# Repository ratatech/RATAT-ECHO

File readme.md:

# RATAT-ECHO

This repository contains mainly the PCB design files for a small echo effect unit. The circuit it's mainly composed by two major blocks, the echo and the spring reverb drive/recovery circuits. 

The echo module is basically an adaptation of the echo circuit included in PT2399 echo processor [datasheet](./datasheets/PT2399_1.pdf). The changes were mostly a few components values to a more standarized ones and the resistor/potentiometer to reduce a bit the minimum delay time. A great analysis of this circuit is done by [Electrosmash](https://www.electrosmash.com/pt2399-analysis). 

The core of the reverb unit is the [ Accutronics, AMC2BF, 2-Spring reverb tank](https://www.amplifiedparts.com/products/reverb-tank-accutronics-amc2bf-2-spring). This is a small and very affordable($9) spring reverb tank. I liked, not only for the budget but also because of the size and the ability to fit the whole tank within the unit box. The drive and recovery circuit was taken from Rod Eliott's design ["Spring Reverb Unit for Guitar"](https://sound-au.com/project34.htm). I added an additional potentiometer a the drive input in order to have some extra input gain. Also a clipping detector was included to have some feedback when pushing too much the input gain. 

## Files

* [datasheets](./datasheets) 	Datasheets of some of the components and schematics used in this project.
* [freecad](./freecad) 			Front panel 3d model design.
* [imgs](./imgs) 				Images used in the design and captures or the 3d models/final pcb.
* [kicad](./kicad) 				Main Kicad project directory. Including schematics and pcb.
* [others](./others) 			Random stuff.

---

## License

- **[MIT license](http://opensource.org/licenses/mit-license.php)**

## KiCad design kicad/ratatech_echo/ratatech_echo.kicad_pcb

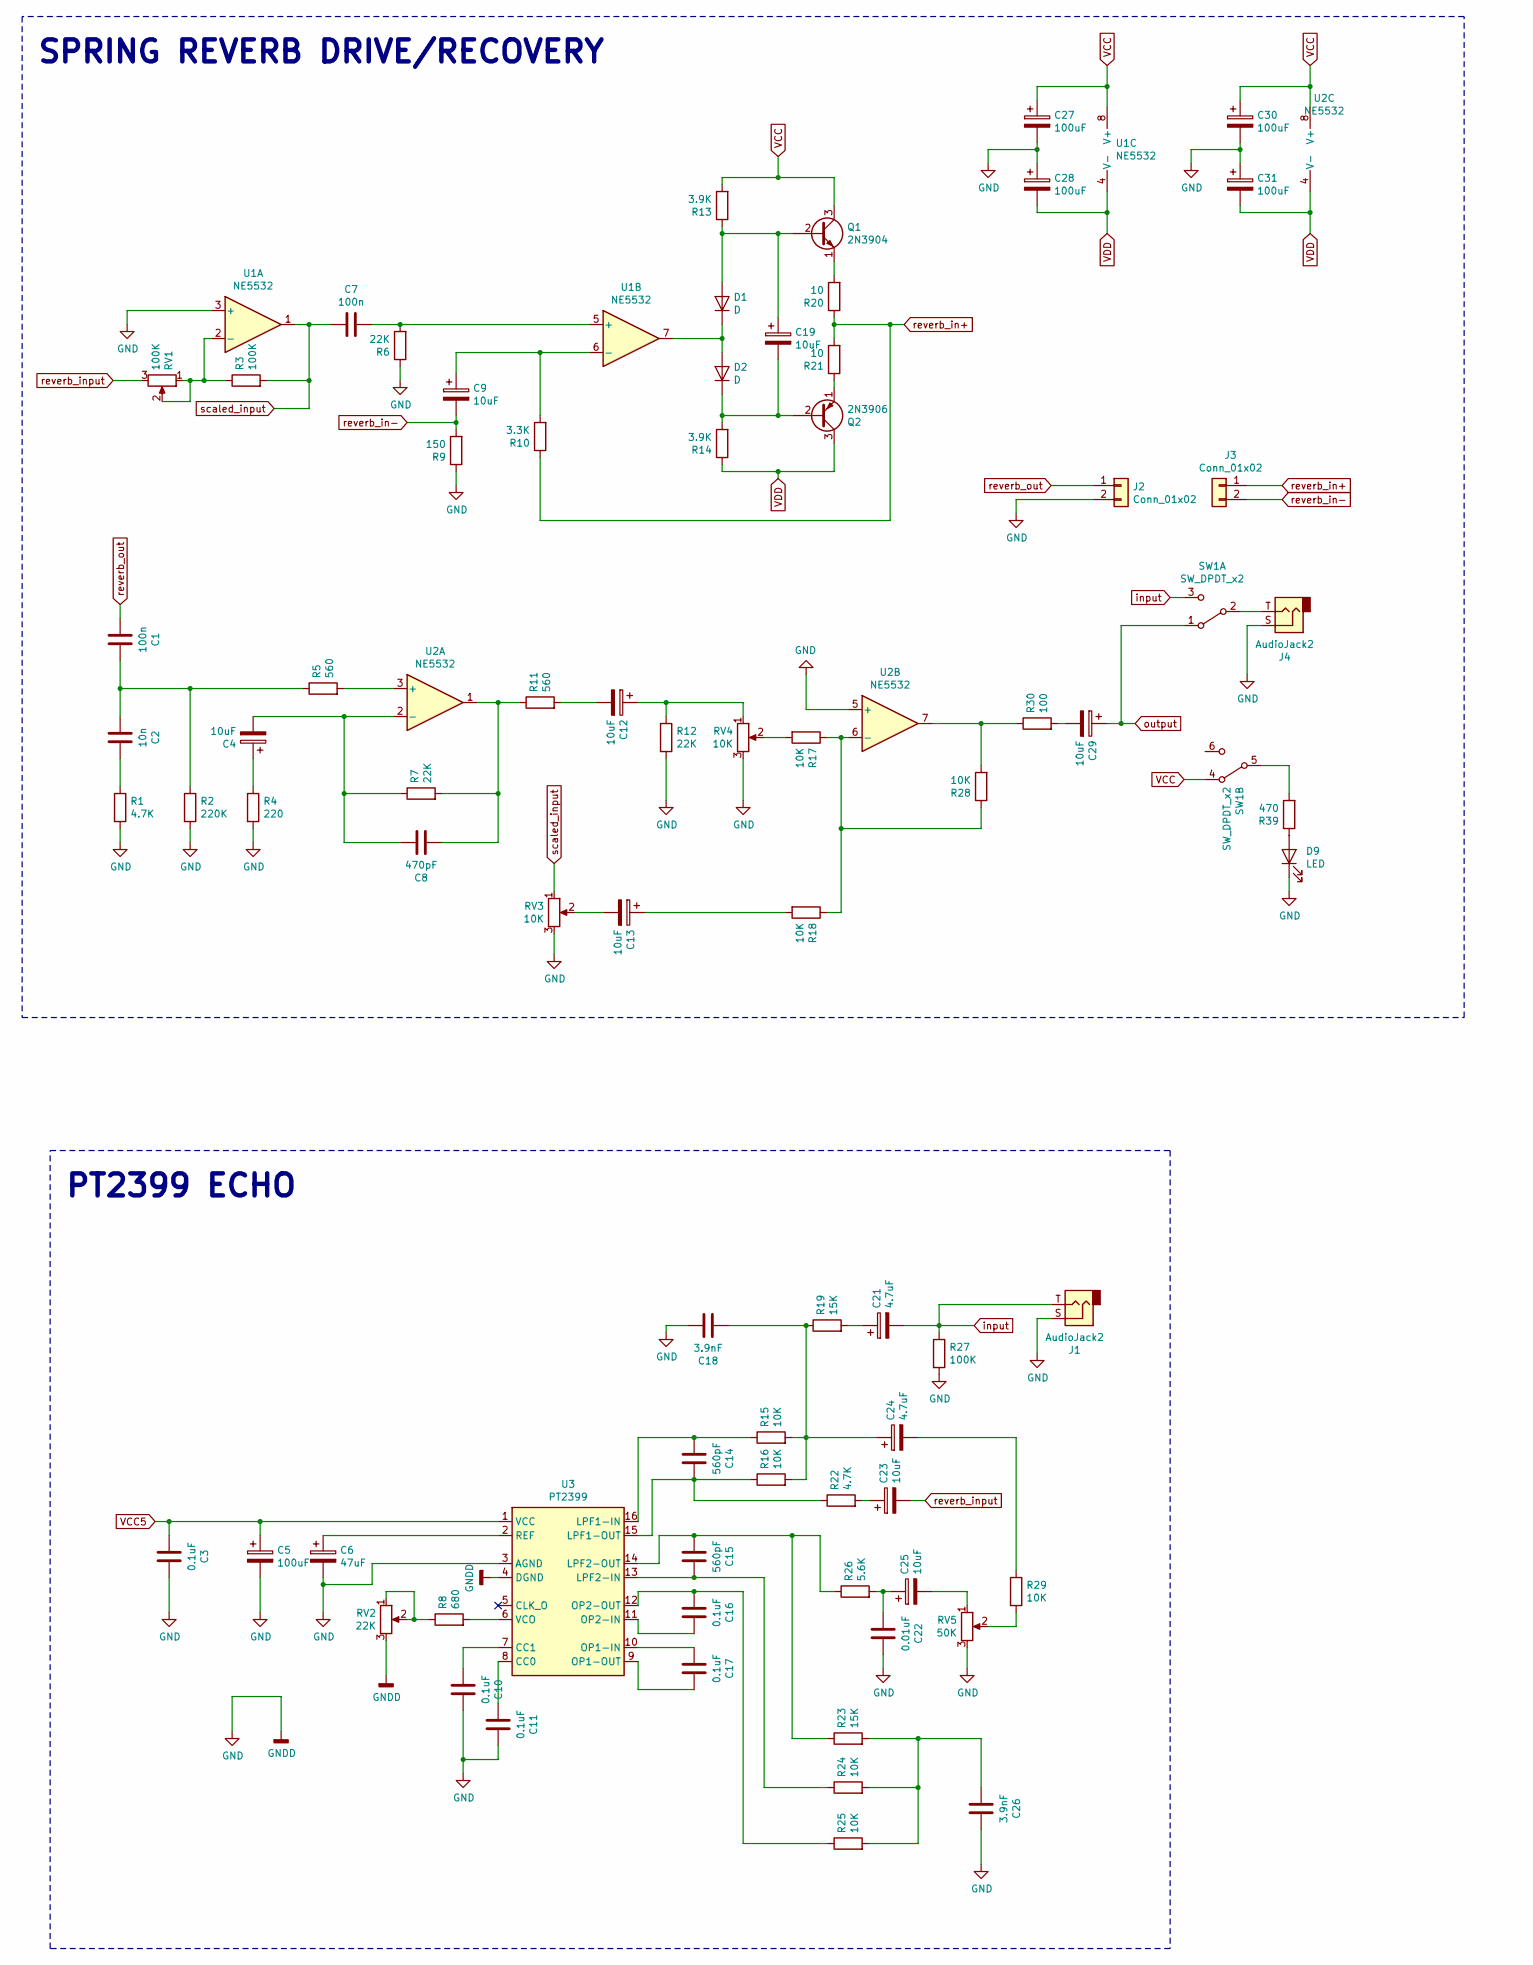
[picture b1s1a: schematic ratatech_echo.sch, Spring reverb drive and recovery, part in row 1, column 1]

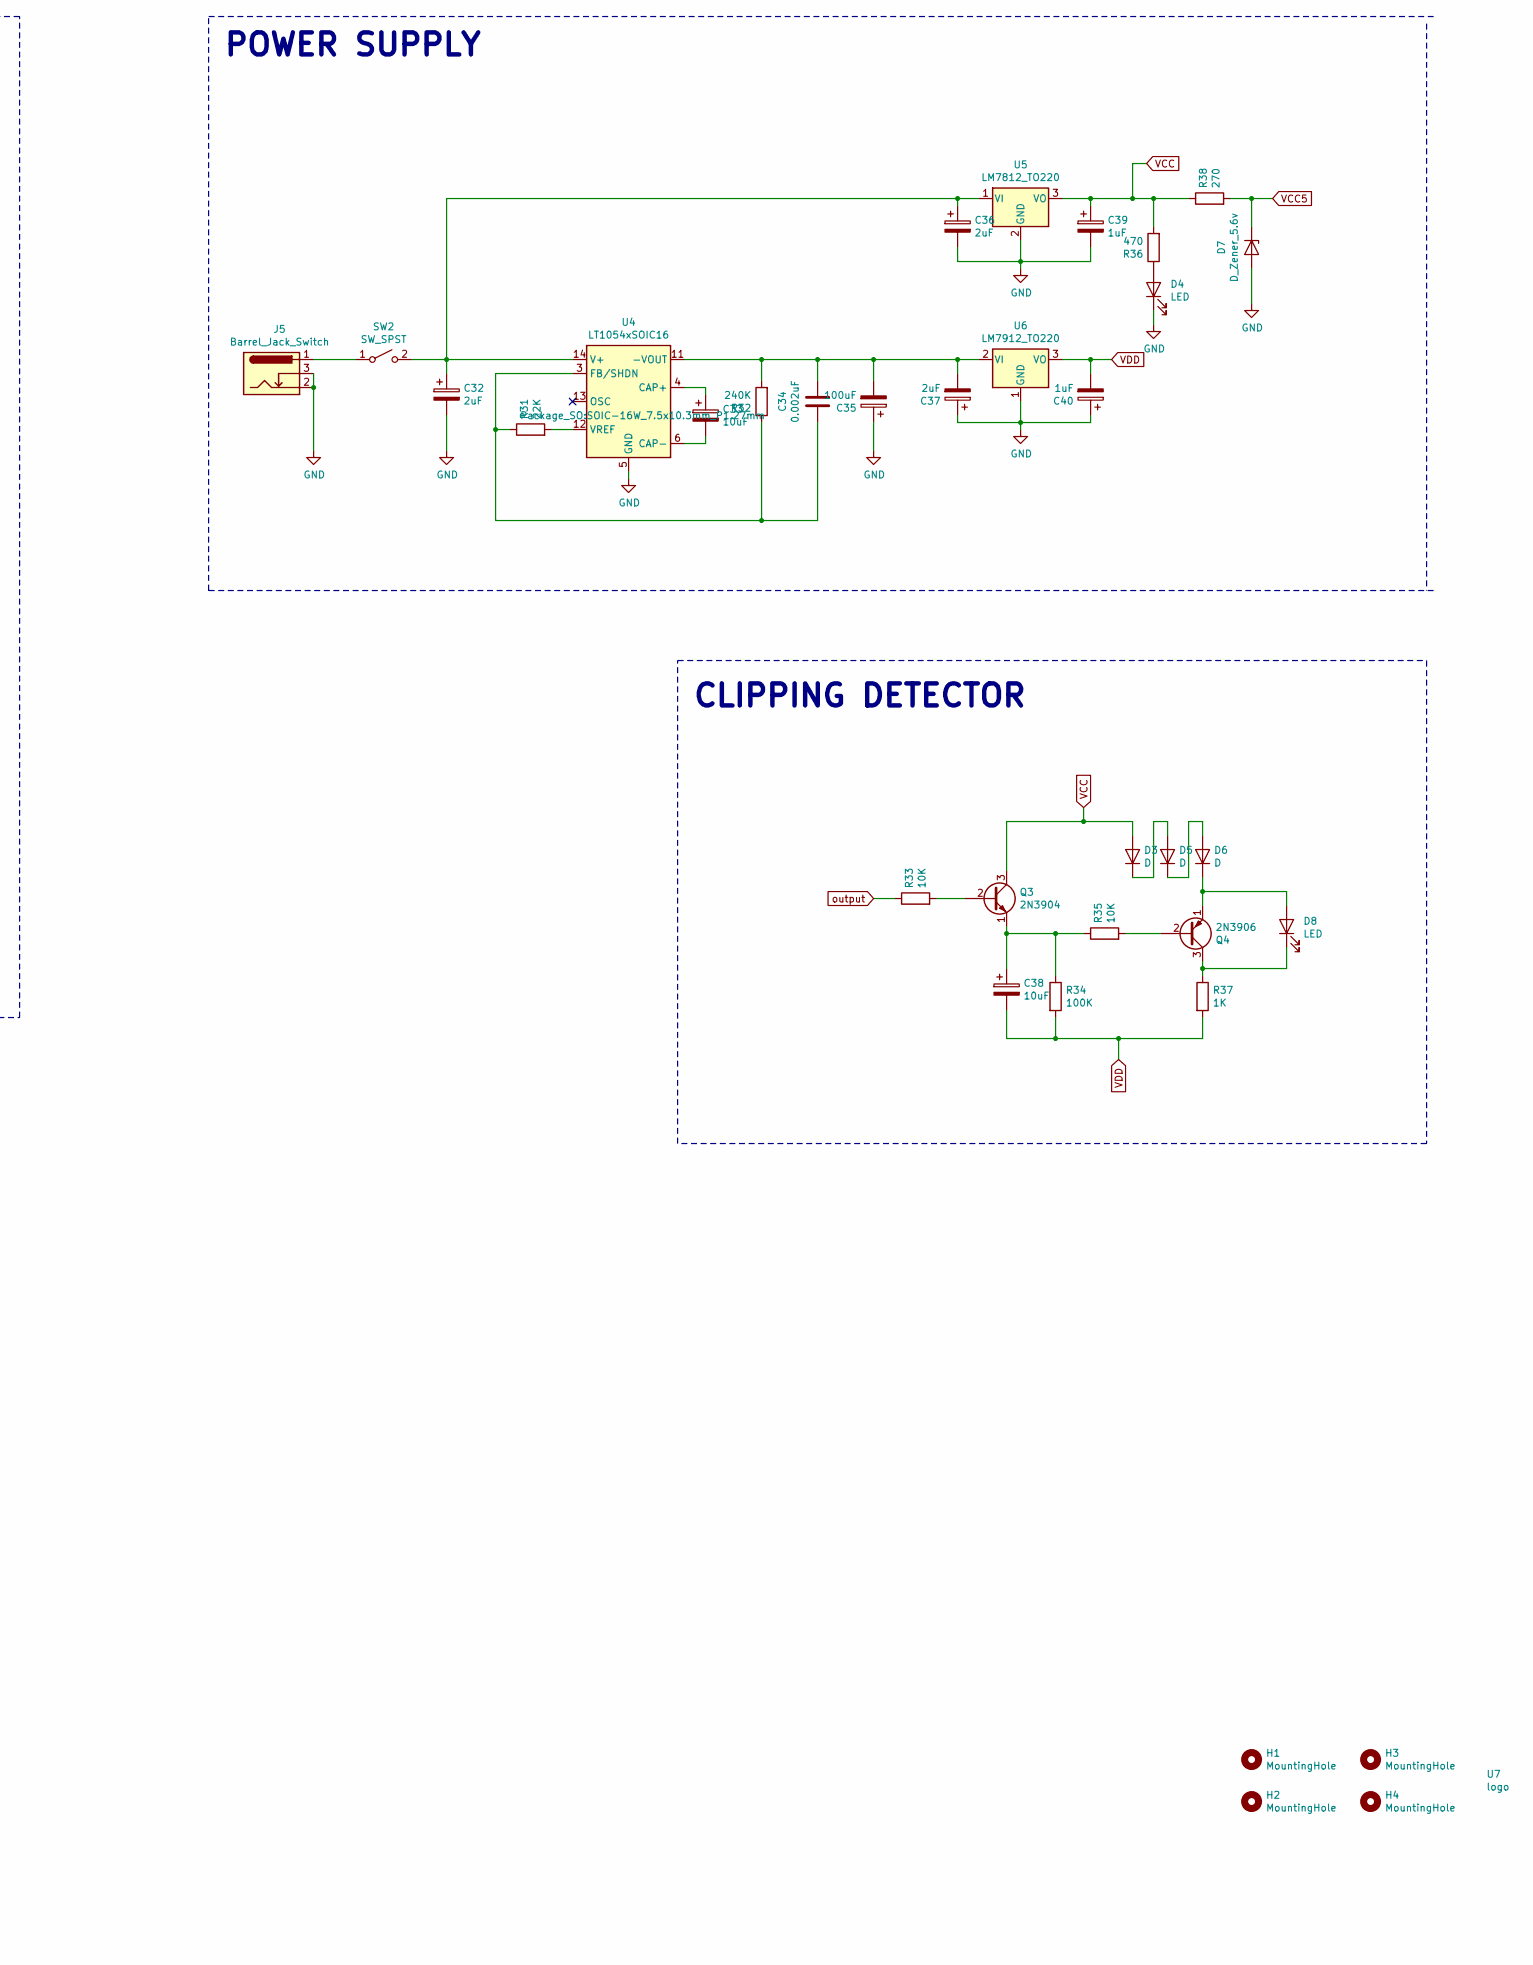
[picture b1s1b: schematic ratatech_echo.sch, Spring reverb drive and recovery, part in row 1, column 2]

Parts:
C1, C7: 100n; C_0603_1608Metric
C2: 10n; C_0603_1608Metric
C3, C10, C11, C16, C17: 0.1uF; C_0603_1608Metric
C4, C9, C12, C13, C19, C23, C25, C29, C33, C38: 10uF; CP_Elec_5x5.3
C5, C27, C28, C30, C31, C35: 100uF; CP_Elec_5x5.3
C6: 47uF; CP_Elec_5x5.3
C8: 470pF; C_0603_1608Metric
C14, C15: 560pF; C_0603_1608Metric
C18, C26: 3.9nF; C_0603_1608Metric
C21, C24: 4.7uF; CP_Elec_5x5.3
C22: 0.01uF; C_0603_1608Metric
C32, C36, C37: 2uF; CP_Elec_5x5.3
C34: 0.002uF; C_0603_1608Metric
C39, C40: 1uF; CP_Elec_5x5.3
D1, D2, D3, D5, D6: D; D_SOT-23_ANK
D4, D8, D9: LED; LED_1206_3216Metric
D7: D_Zener_5.6v; D_SOD-323
H1, H2, H3, H4: MountingHole; MountingHole_3mm
J1, J4: AudioJack2; Jack_6.35mm_Neutrik_NRJ4HF-1_Horizontal
J2, J3: Conn_01x02; JST_EH_S2B-EH_1x02_P2.50mm_Horizontal
J5: Barrel_Jack_Switch; BarrelJack_CUI_PJ-102AH_Horizontal
Q1, Q3: 2N3904; SOT-23
Q2, Q4: 2N3906; SOT-23
R1, R22: 4.7K; R_0603_1608Metric
R2: 220K; R_0603_1608Metric
R3, R27, R34: 100K; R_0603_1608Metric
R4: 220; R_0603_1608Metric
R5, R11: 560; R_0603_1608Metric
R6, R7, R12, R31: 22K; R_0603_1608Metric
R8: 680; R_0603_1608Metric
R9: 150; R_0603_1608Metric
R10: 3.3K; R_0603_1608Metric
R13, R14: 3.9K; R_0603_1608Metric
R15, R16, R17, R18, R24, R25, R28, R29, R33, R35: 10K; R_0603_1608Metric
R19, R23: 15K; R_0603_1608Metric
R20, R21: 10; R_0603_1608Metric
R26: 5.6K; R_0603_1608Metric
R30: 100; R_0603_1608Metric
R32: 240K; R_0603_1608Metric
R36, R39: 470; R_0603_1608Metric
R37: 1K; R_0603_1608Metric
R38: 270; R_0603_1608Metric
RV1: 100K; Potentiometer_Alps_RK09K_Single_Vertical
RV2: 22K; Potentiometer_Alps_RK09K_Single_Vertical
RV3, RV4: 10K; Potentiometer_Alps_RK09K_Single_Vertical
RV5: 50K; Potentiometer_Alps_RK09K_Single_Vertical
SW1: SW_DPDT_x2; M2028B2B1W03
SW2: SW_SPST; SW_CuK_OS102011MA1QN1_SPDT_Angled
U1, U2: NE5532; SOIC-8_3.9x4.9mm_P1.27mm
U3: PT2399; DIP-16_W8.89mm_SMDSocket_LongPads
U4: LT1054xSOIC16; SOIC-16W_7.5x10.3mm_P1.27mm
U5: LM7812_TO220; ATPAK-2
U6: LM7912_TO220; ATPAK-2
U7: logo; ratatech_bitmap

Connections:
GND: C3.1, C5.2, C6.2, C10.1, C11.1, C18.1, C22.1, C26.1, C27.2, C28.1, C30.2, C31.1, C32.2, C35.1, C36.2, C37.1, C39.2, C40.1, D4.1 (K), D7.2 (A), D9.1 (K), J1.S, J2.2, J4.S, J5.2, J5.3, R1.2, R2.2, R4.2, R6.1, R9.1, R12.2, R27.2, RV2.3, RV3.3, RV4.3, RV5.3, U1.3 (+), U2.5 (+), U3.3 (AGND), U3.4 (DGND), U4.5 (GND), U5.2 (GND), U6.1 (GND)
unnamed: C1.1, C2.2, R2.1, R5.1
unnamed: C2.1, R1.1
unnamed: C4.1, R4.1
unnamed: C4.2, C8.1, R7.1, U2.2 (-)
unnamed: C6.1, U3.2 (REF)
unnamed: C7.1, R6.2, U1.5 (+)
unnamed: C8.2, R7.2, R11.1, U2.1
unnamed: C9.1, R10.2, U1.6 (-)
unnamed: C10.2, U3.7 (CC1)
unnamed: C11.2, U3.8 (CC0)
unnamed: C12.1, R12.1, RV4.1
unnamed: C12.2, R11.2
unnamed: C13.1, R18.2
unnamed: C13.2, RV3.2
unnamed: C14.1, R16.1, R22.1, U3.15 (LPF1-OUT)
unnamed: C14.2, R15.1, U3.16 (LPF1-IN)
unnamed: C15.1, R24.1, U3.13 (LPF2-IN)
unnamed: C15.2, R23.1, R26.1, U3.14 (LPF2-OUT)
unnamed: C16.1, U3.11 (OP2-IN)
unnamed: C16.2, R25.1, U3.12 (OP2-OUT)
unnamed: C17.1, U3.9 (OP1-OUT)
unnamed: C17.2, U3.10 (OP1-IN)
unnamed: C18.2, C24.1, R15.2, R16.2, R19.1
unnamed: C19.1, D1.2 (A), Q1.2 (B), R13.1
unnamed: C19.2, D2.1 (K), Q2.2 (B), R14.2
unnamed: C21.1, R19.2
unnamed: C22.2, C25.1, R26.2
unnamed: C23.1, R22.2
unnamed: C24.2, R29.1
unnamed: C25.2, RV5.1
unnamed: C26.2, R23.2, R24.2, R25.2
unnamed: C29.2, R30.2
unnamed: C32.1, C36.1, SW2.2 (B), U4.14 (V+), U5.1 (VI)
unnamed: C33.1, U4.4 (CAP+)
unnamed: C33.2, U4.6 (CAP-)
unnamed: C34.1, C35.2, C37.2, R32.2, U4.11 (-VOUT), U6.2 (VI)
unnamed: C34.2, R31.1, R32.1, U4.3 (FB/SHDN)
unnamed: C38.1, Q3.1 (E), R34.1, R35.1
unnamed: D1.1 (K), D2.2 (A), U1.7
unnamed: D3.1 (K), D5.2 (A)
unnamed: D4.2 (A), R36.1
unnamed: D5.1 (K), D6.2 (A)
unnamed: D6.1 (K), D8.2 (A), Q4.1 (E)
unnamed: D8.1 (K), Q4.3 (C), R37.1
unnamed: D9.2 (A), R39.1
unnamed: J4.T, SW1.2 (B)
unnamed: J5.1, SW2.1 (A)
unnamed: Q1.1 (E), R20.2
unnamed: Q2.1 (E), R21.1
unnamed: Q3.2 (B), R33.2
unnamed: Q4.2 (B), R35.2
unnamed: R3.1, RV1.1, RV1.2, U1.2 (-)
unnamed: R5.2, U2.3 (+)
unnamed: R8.1, RV2.1, RV2.2
unnamed: R8.2, U3.6 (VCO)
unnamed: R17.1, R18.1, R28.1, U2.6 (-)
unnamed: R17.2, RV4.2
unnamed: R28.2, R30.1, U2.7
unnamed: R29.2, RV5.2
unnamed: R31.2, U4.12 (VREF)
unnamed: R39.2, SW1.5 (B)
VCC: C27.1, C30.1, C39.1, D3.2 (A), Q1.3 (C), Q3.3 (C), R13.2, R36.2, R38.1, SW1.4 (A), U1.8 (V+), U2.8 (V+), U5.3 (VO)
VCC5: C3.2, C5.1, D7.1 (K), R38.2, U3.1 (VCC)
VDD: C28.2, C31.2, C38.2, C40.2, Q2.3 (C), R14.1, R34.2, R37.2, U1.4 (V-), U2.4 (V-), U6.3 (VO)
input: C21.2, J1.T, R27.1, SW1.3 (C)
output: C29.1, R33.1, SW1.1 (A)
reverb_in+: J3.1, R10.1, R20.1, R21.2
reverb_in-: C9.2, J3.2, R9.2
reverb_input: C23.2, RV1.3
reverb_out: C1.2, J2.1
scaled_input: C7.2, R3.2, RV3.1, U1.1

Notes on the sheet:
CLIPPING DETECTOR
PT2399 ECHO
SPRING REVERB DRIVE/RECOVERY
POWER SUPPLY

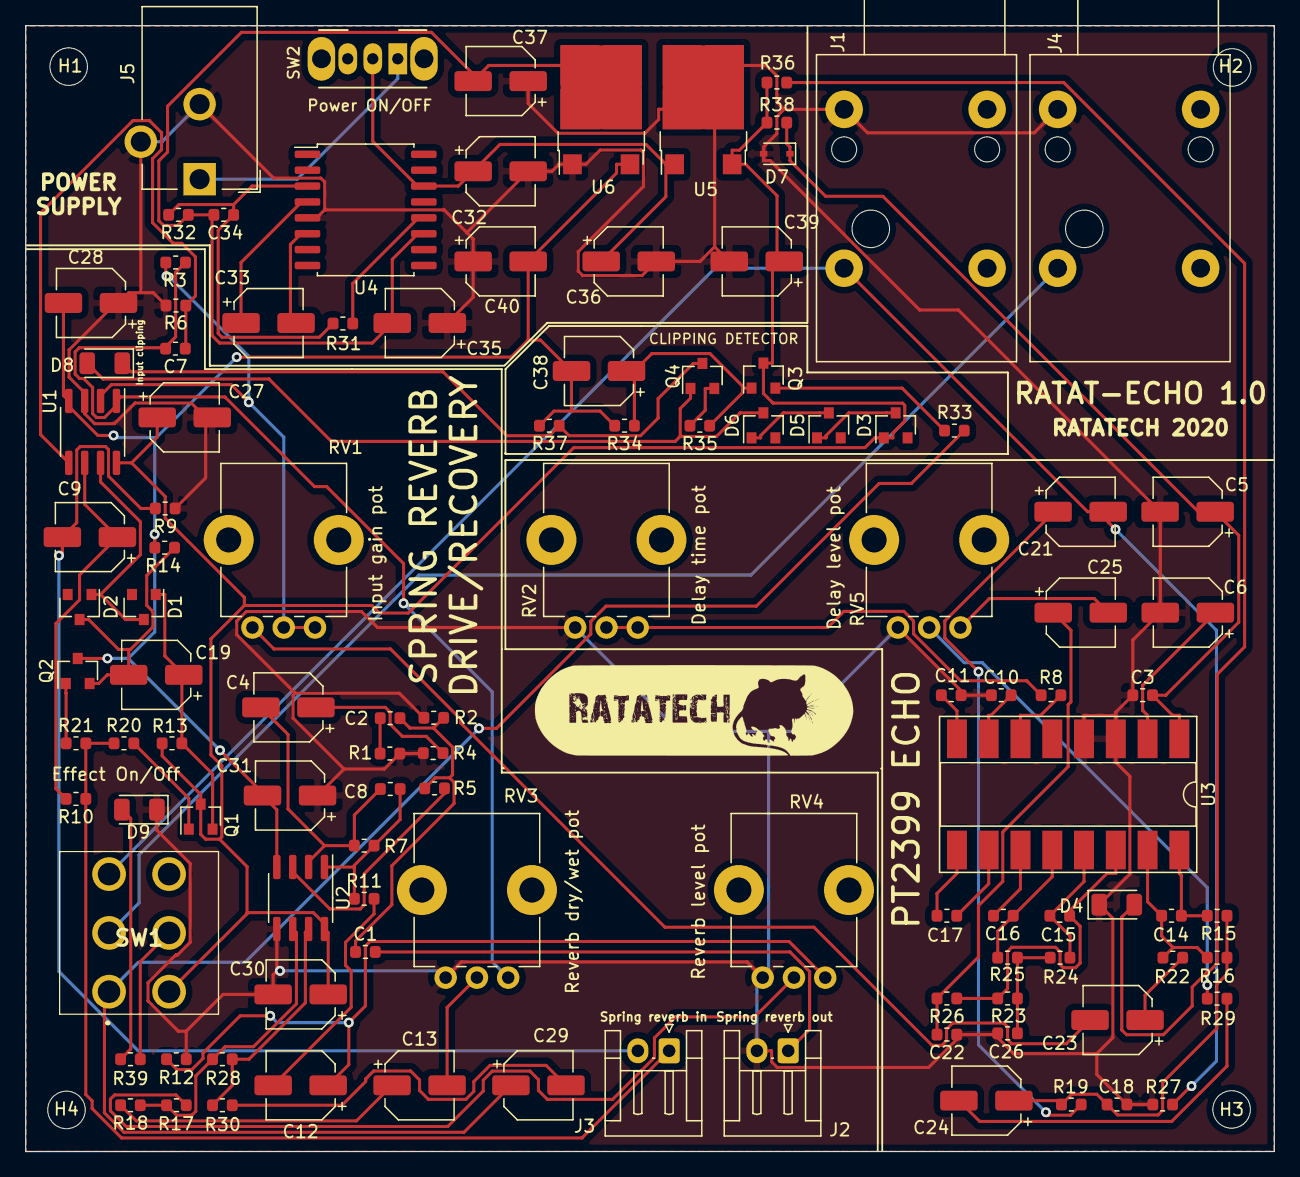
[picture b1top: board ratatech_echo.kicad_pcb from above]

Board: 2 copper layers, 99.8 x 90.0 mm, 114 parts (0 on the bottom side), 72 nets.

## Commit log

2020-05-14 init repo
2020-05-20 Routing full done first try
2020-05-20 Removed useless files
2020-05-21 Added readme
2020-05-21 Changed readme template
2020-05-21 Top pcb img changes1
2020-05-21 Readme doc WIP
2020-05-21 Fix readme doc links
2020-05-22 Added small spring reverb description
2020-06-07 Component rearrengement
2020-06-09 Autorouting done
2020-06-09 PCB done v1.0. Generated gerbers for fab
2020-06-11 Added mouser part numbers
2020-06-14 Finished BOM with mouser part numbers
